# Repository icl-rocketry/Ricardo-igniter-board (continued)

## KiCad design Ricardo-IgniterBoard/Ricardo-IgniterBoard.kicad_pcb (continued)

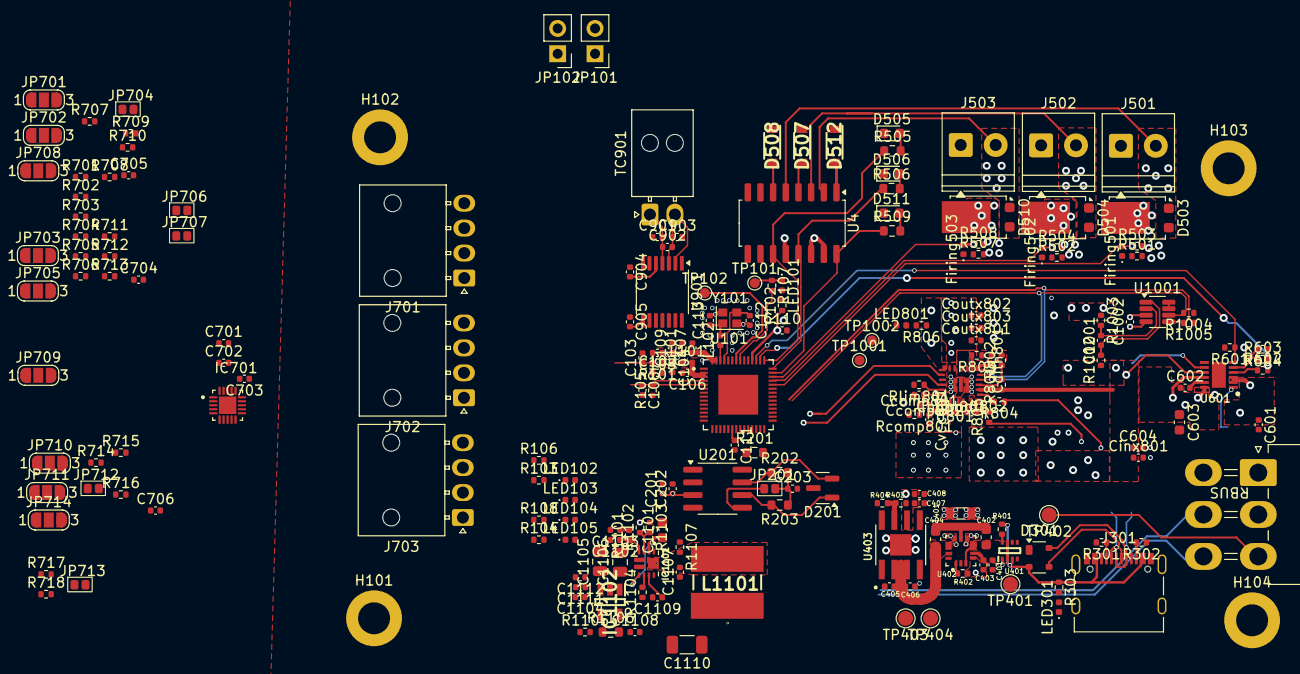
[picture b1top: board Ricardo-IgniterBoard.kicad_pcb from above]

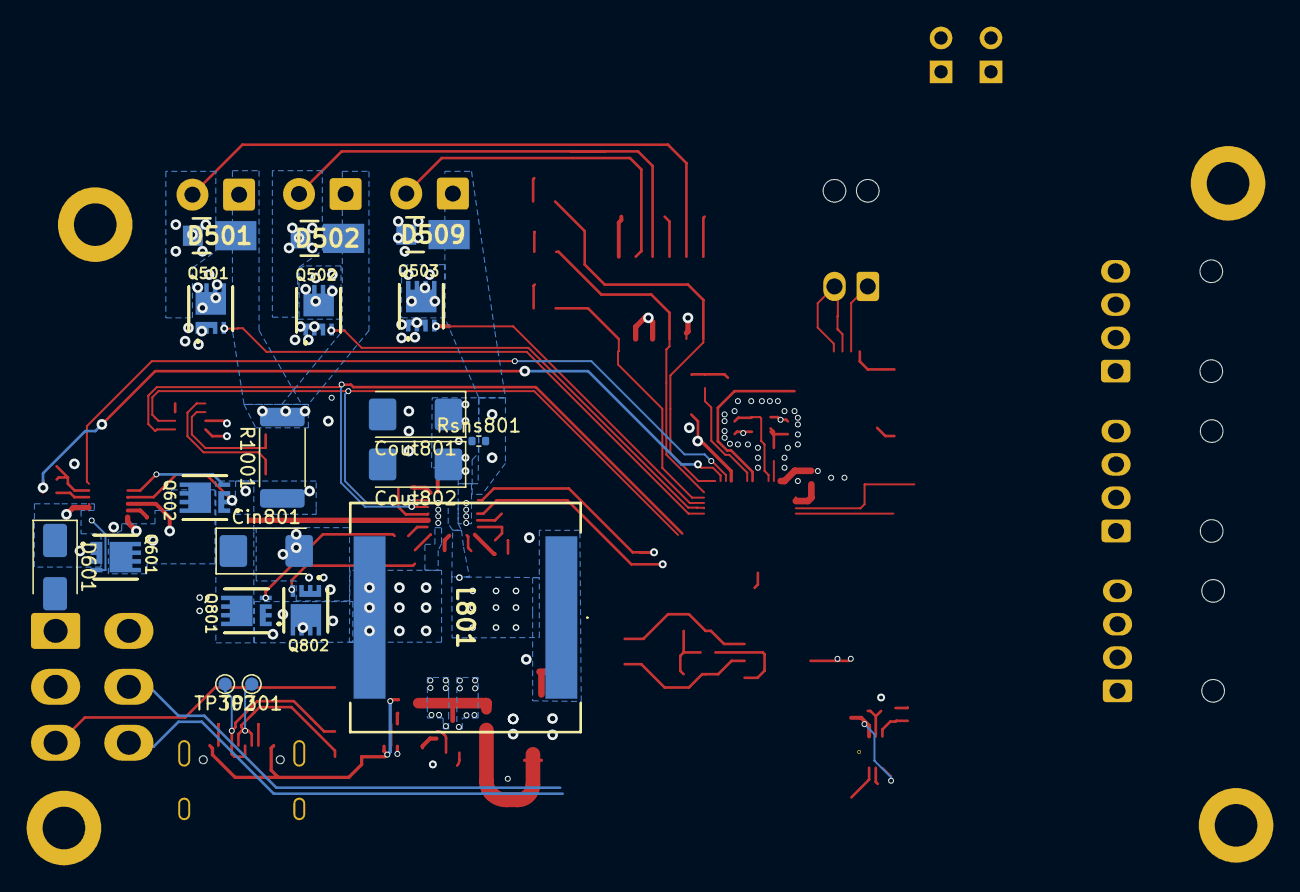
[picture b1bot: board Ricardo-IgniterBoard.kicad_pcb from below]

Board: 4 copper layers, 227 parts (19 on the bottom side), 149 nets.

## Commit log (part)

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2026-02-10 Clone from template
2026-02-14 Adding pre-existing sheets
    Added pyro, high-side master switch and pt sensor
2026-02-28 Adjusting numbers and adding hieratical pins
    Adjusted number of pyro and PT modules and connected everything to the root
2026-04-06 Added Voltage Regulator
2026-04-07 Little touches
2026-04-11 Test
2026-04-12 Fixed?
2026-04-14 Auto stash before merge of "icl-rocketry/main" and "main"
2026-04-19 Assigning components
    And added the thermocouple
2026-05-06 Fixed tc and igniter power
2026-05-12 some more changes
    added current sensor for solenoid, fixed optocouplers
2026-05-12 input filter
    added to current sensor
2026-05-16 added test points on input filter
2026-06-09 Assigning footprints
    and adding them to layout
2026-06-29 Not much tbh
